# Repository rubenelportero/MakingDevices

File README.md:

# MakingDevices
https://makingdevices.com/

Available Projects:

*********************************************************************************************
Pic Bytes Micro

Pic Bytes Micro is an 8-bit portable arcade with a monochromatic LED screen. The project was chosen in order to learn about different engineering fields: Basic electronics, microcontrollers and programming. Some games are developed for the hardware: Snake, Tetris, Arkanoid...

Everything you will find here is free and open: Software, Hardware and documentation

Date: 23/08/2020
*********************************************************************************************

*********************************************************************************************
Bytes Counter

Bytes Counter is just a Digital Tally Counter. The project was chosen to test some PCB manufacturer capabilities and experiment with both the XLP (Extreme Low-Power Technology) and the pic18LF14k50 itself.

Everything you will find here is free and open: Software, Hardware and documentation

Date: 16/08/2021
*********************************************************************************************

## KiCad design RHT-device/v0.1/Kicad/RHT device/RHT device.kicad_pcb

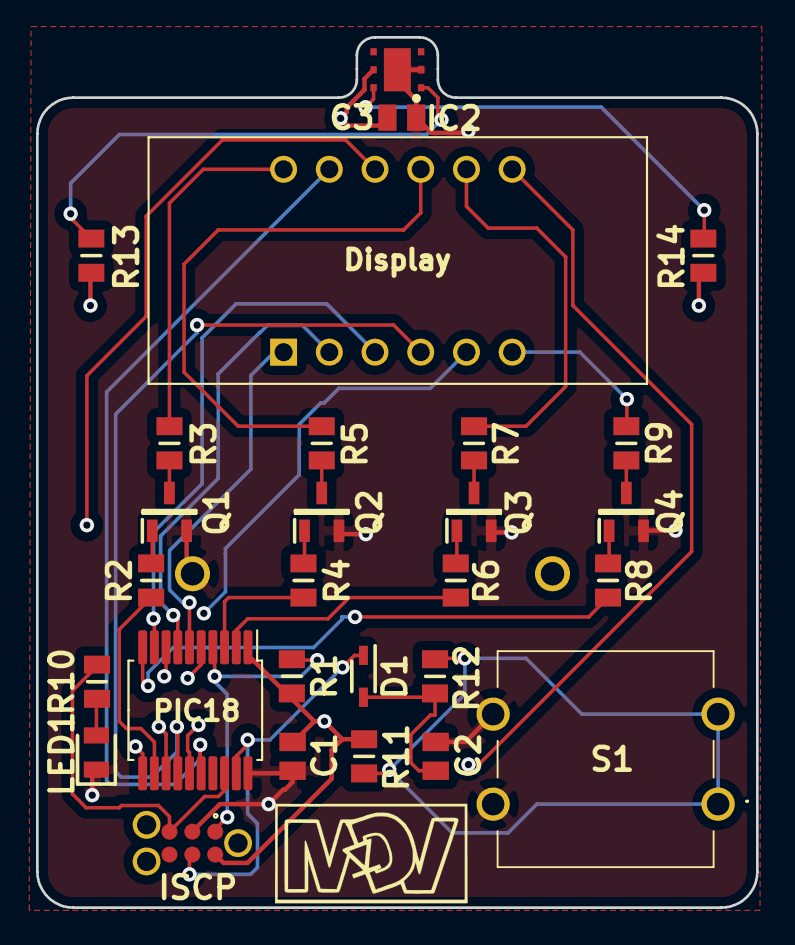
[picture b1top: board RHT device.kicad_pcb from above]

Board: 4 copper layers, 40.0 x 48.4 mm, 29 parts (1 on the bottom side), 34 nets.

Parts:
C1, C2, C3: 100nF; CAPC2012X140N
D1: ZLLS410TA; SOD2513X120N
IC1: PIC18LF14K50-I_SO; SSOP-20_5.3x7.2mm_P0.65mm
IC2: HTU20D; SON50P250X250X100-9N-D
ISCP: TC2030-MCP-NL
LED1: LTST-C171GKT; LEDC2012X90N
Q1, Q2, Q3, Q4: SMMBT5551LT1G; SOT96P237X111-3N
R1, R11, R12, R13, R14: 10k; RESC2012X75N
R2, R4, R6, R8: 4k7; RESC2012X75N
R3, R5, R7, R9: 100; RESC2012X75N
R10: 220; RESC2012X75N
S1: B3F-4050-SamacSys_Parts; B3F4050
U1: CC56-12EWA; CA56-12EWA
U2: CH075-2032; CH0752032

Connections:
+3V: C1.1, C3.2, IC1.1, IC2.5, ISCP.2, R1.1, R11.2, R13.2, R14.1, U2.1
/B_1: D1.1, IC1.19, ISCP.4
/CC_1: R3.2, U1.12
/CC_2: R5.2, U1.9
/CC_3: R7.2, U1.8
/CC_4: R9.2, U1.6
/C_1: IC1.12, R2.1
/C_2: IC1.3, R4.1
/C_3: IC1.2, R6.1
/C_4: IC1.10, R8.1
/D_a: IC1.16, U1.11
/D_b: IC1.15, U1.7
/D_c: IC1.14, U1.4
/D_d: IC1.7, U1.2
/D_dp: IC1.9, U1.3
/D_e: IC1.6, U1.1
/D_f: IC1.5, U1.10
/D_g: IC1.8, U1.5
/I2C_DATA: IC1.13, IC2.1, R13.1
/I2C_SCK: IC1.11, IC2.6, R14.2
/MCLR: IC1.4, ISCP.1, R1.2
/PGC: IC1.18, ISCP.5, R10.1
unnamed: C2.1, D1.2, R12.2
unnamed: LED1.2, R10.2
unnamed: Q1.1, R2.2
unnamed: Q1.3, R3.1
unnamed: Q2.1, R4.2
unnamed: Q2.3, R5.1
unnamed: Q3.1, R6.2
unnamed: Q3.3, R7.1
unnamed: Q4.1, R8.2
unnamed: Q4.3, R9.1
unnamed: R11.1, R12.1, S1.1, S1.3
gnd: C1.2, C2.2, C3.1, IC1.20, IC2.2, IC2.7, ISCP.3, LED1.1, Q1.2, Q2.2, Q3.2, Q4.2, S1.2, S1.4, U2.2

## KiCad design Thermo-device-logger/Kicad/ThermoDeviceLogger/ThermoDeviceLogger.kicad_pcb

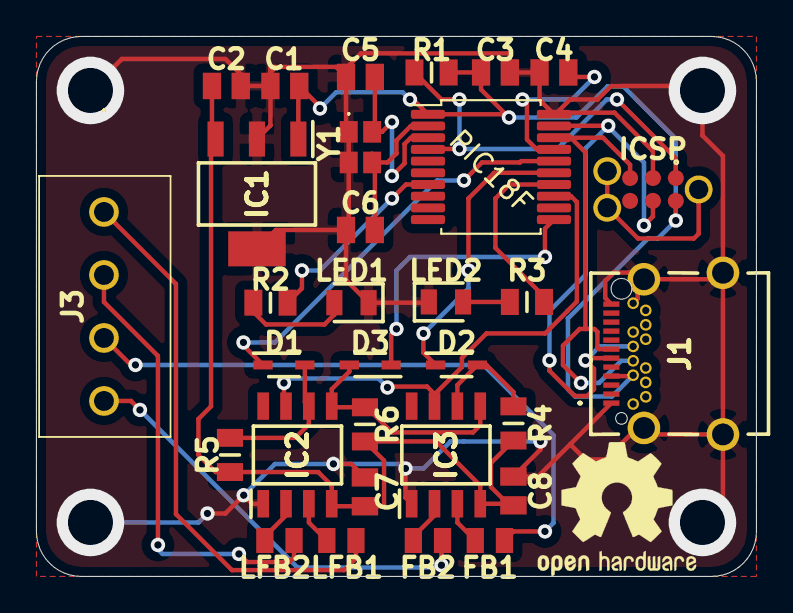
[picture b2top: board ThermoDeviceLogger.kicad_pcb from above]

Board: 2 copper layers, 40.0 x 30.0 mm, 31 parts (0 on the bottom side), 28 nets.

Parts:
C1, C2, C3, C4: 1uF; CAPC2012X140N
C5, C6: 22pF; CAPC2012X140N
C7, C8: 100nF; CAPC2012X140N
D1, D2, D3: ZLLS410TA; SOD2513X120N
FB1, FB2: 742792005; CAPC2012X90N
IC1: TC1108-3.3VDBTR; SOT230P700X180-4N
IC2, IC3: MAX31855KASA+; SOIC127P600X175-8N
J1: Type - C; 2171830001
J2: TC2030-MCP-NL
J3: 4-terminal; 1751264
LED1, LED2: Green; LEDC2012X90N
LFB1, LFB2: Ferrite; CAPC2012X90N
R1, R4, R5, R6: 10k; RESC2012X75N
R2, R3: 220; RESC2012X75N
U1: PIC18F; SSOP-20_5.3x7.2mm_P0.65mm
Y1: 12Mhz; CX2520DB12000D0GPSC1

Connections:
+5V: C1.1, C3.2, IC1.1, J1.A4, J1.B9, J2.2, R1.1, U1.1
/3.3V: C2.1, C7.2, C8.2, IC1.3, IC2.4, IC3.4, R4.1, R5.1, R6.1
/CS_1: D1.1, U1.16
/CS_2: D2.1, U1.15
/Crystal2: C6.2, U1.2, Y1.3
/Cyrstal1: C5.1, U1.3, Y1.4
/MCLR: J2.1, R1.2, U1.4
/MISO: IC2.7, IC3.7, U1.13
/PGC: J1.A7, J1.B7, J2.5, U1.18
/PGD: J1.A6, J1.B6, J2.4, U1.19
/SCK: D3.1, U1.11
/ThermoCouple Modules/T+tcm1: J3.1, LFB1.1
/ThermoCouple Modules/T+tcm2: FB1.1, J3.3
/ThermoCouple Modules/T-tcm1: J3.2, LFB2.1
/ThermoCouple Modules/T-tcm2: FB2.1, J3.4
GND: C1.2, C2.2, C3.1, C4.1, C5.2, C6.1, C7.1, C8.1, IC1.2, IC1.4, IC2.1, IC3.1, J1.A1, J1.A12, J1.B1, J1.MH1, J1.MH2, J1.MH3, J1.MH4, J2.3, LED1.1, LED2.1, U1.20, Y1.1, Y1.2
unnamed: C4.2, U1.17
unnamed: D1.2, IC2.6, R5.2
unnamed: D2.2, IC3.6, R4.2
unnamed: D3.2, IC2.5, IC3.5, R6.2
unnamed: FB1.2, IC3.3
unnamed: FB2.2, IC3.2
unnamed: IC2.2, LFB2.2
unnamed: IC2.3, LFB1.2
unnamed: LED1.2, R2.2
unnamed: LED2.2, R3.2
unnamed: R2.1, U1.7
unnamed: R3.1, U1.14

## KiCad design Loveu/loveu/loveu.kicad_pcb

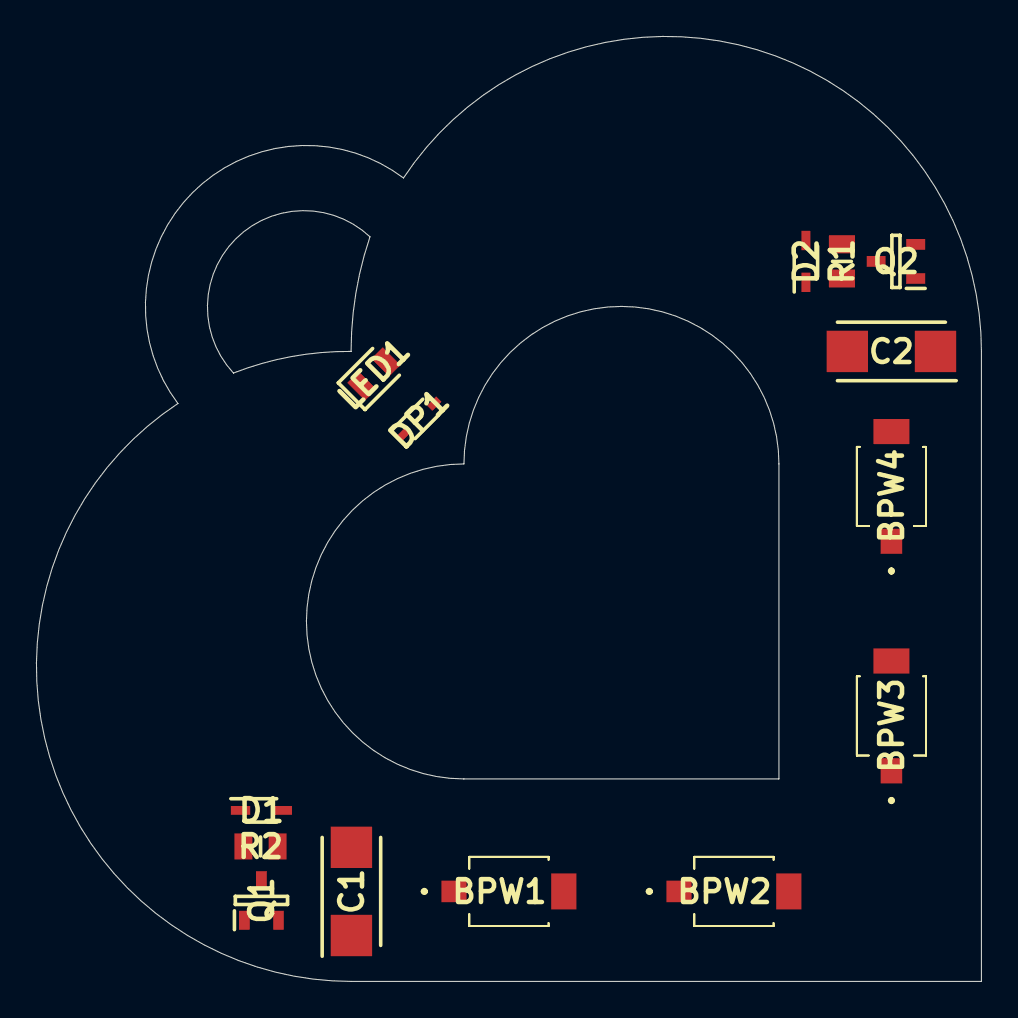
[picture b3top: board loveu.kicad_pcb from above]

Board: 2 copper layers, 52.5 x 52.5 mm, 14 parts (0 on the bottom side), 11 nets, no tracks yet.

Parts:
BPW1, BPW2, BPW3, BPW4: BPW_34_SR-Z; BPW34SRZ
C1, C2: 100uF; CAPPM6032X280N
D1, D2: ZLLS410TA; SOD2513X120N
DP1: BAV21WS_R1_00001; SODFL2512X90N
LED1: SML-H12V8TT86; LEDC2012X90N
Q1: BCX70; SOT95P230X110-3N
Q2: BC857; SOT95P230X110-3N
R1: 4k7; RESC2012X75N
R2: 220; RESC2012X75N

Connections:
unnamed: BPW1.1, C2.1, D1.2, Q2.2
unnamed: BPW1.2, BPW2.1
unnamed: BPW2.2, BPW3.1
unnamed: BPW3.2, BPW4.1
unnamed: BPW4.2, C1.2, D2.1, Q2.3
unnamed: C1.1, D1.1, LED1.2, R1.1
unnamed: C2.2, D2.2, Q1.2
unnamed: DP1.1, Q1.1
unnamed: DP1.2, R1.2
unnamed: LED1.1, R2.1
unnamed: Q1.3, Q2.1, R2.2

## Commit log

2020-08-23 Add files via upload
    Beta version Pic Bytes Micro
2020-08-23 removing outdated files
2020-08-23 changing name
2021-08-12 New Project
    v0.1a
2021-08-16 Update README.md
    update
2021-08-16 Update
    Small Update
2021-10-26 Updated to v1
    Fix bugs**
    See https://makingdevices.com post for the list of the updatedes
2021-11-17 All projects
    Update projects
2021-11-17 Update!
2021-11-17 Last update
